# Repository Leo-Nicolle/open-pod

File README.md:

# opentone

Work in progress.

This is a mp3 player in the style of an ipod classic. 

### Hardware
 - MCU: ESP32
 - Display: 2.2" LCD
 - SD Card: MicroSD
 - Audio: VS1063
 - Click wheel: MPR121

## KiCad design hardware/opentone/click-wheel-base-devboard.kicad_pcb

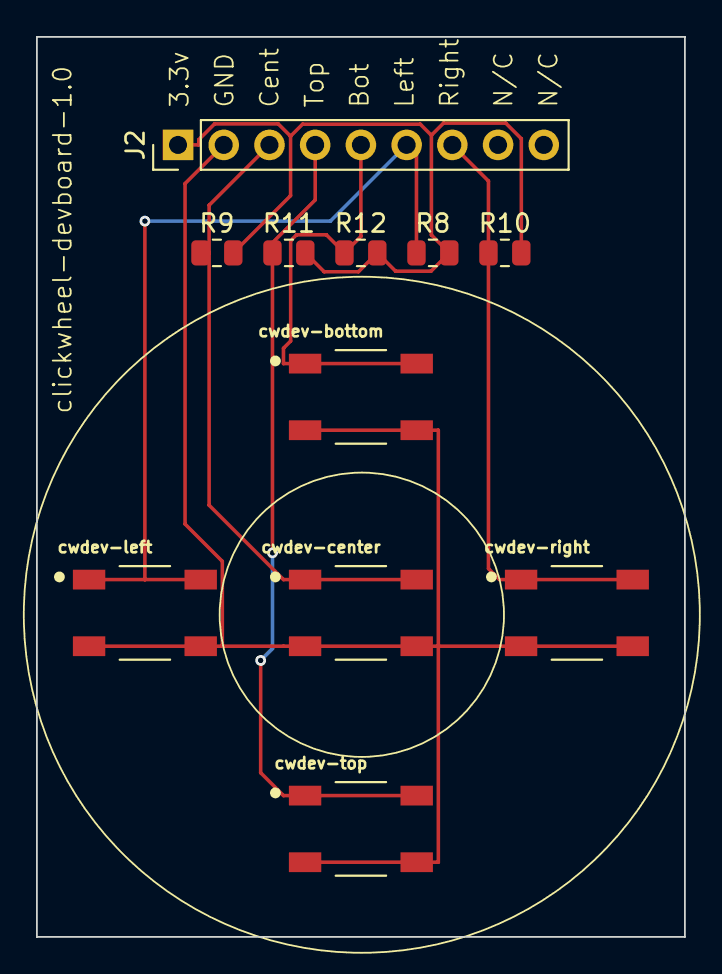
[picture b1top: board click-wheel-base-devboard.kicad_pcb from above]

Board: 2 copper layers, 36.0 x 50.0 mm, 11 parts (0 on the bottom side), 7 nets.

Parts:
J2: Conn_01x09; PinHeader_1x09_P2.54mm_Vertical
R8, R9, R10, R11, R12: 10k; R_0805_2012Metric
cwdev-bottom: SKQGAFE010; SW_SKQGAFE010
cwdev-center: SKQGAFE010; SW_SKQGAFE010
cwdev-left: SKQGAFE010; SW_SKQGAFE010
cwdev-right: SKQGAFE010; SW_SKQGAFE010
cwdev-top: SKQGAFE010; SW_SKQGAFE010

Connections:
+3.3V: J2.1, R8.2, R9.2, R10.2, R11.2, R12.2
GND: J2.2, cwdev-bottom.3, cwdev-bottom.4, cwdev-center.3, cwdev-center.4, cwdev-left.3, cwdev-left.4, cwdev-right.3, cwdev-right.4, cwdev-top.3, cwdev-top.4
SW_BOTTOM: J2.5, R12.1, cwdev-bottom.1, cwdev-bottom.2
SW_CENTER: J2.3, R9.1, cwdev-center.1, cwdev-center.2
SW_LEFT: J2.6, R8.1, cwdev-left.1, cwdev-left.2
SW_RIGHT: J2.7, R10.1, cwdev-right.1, cwdev-right.2
SW_TOP: J2.4, R11.1, cwdev-top.1, cwdev-top.2

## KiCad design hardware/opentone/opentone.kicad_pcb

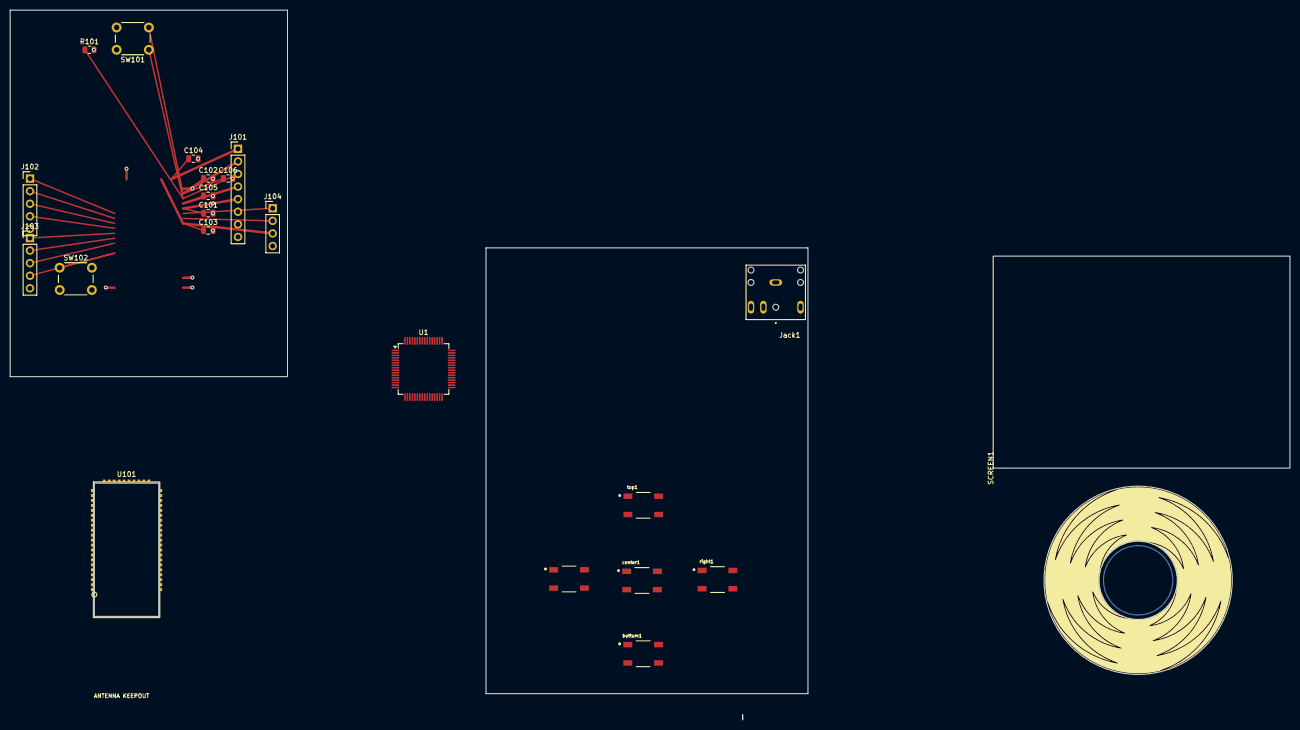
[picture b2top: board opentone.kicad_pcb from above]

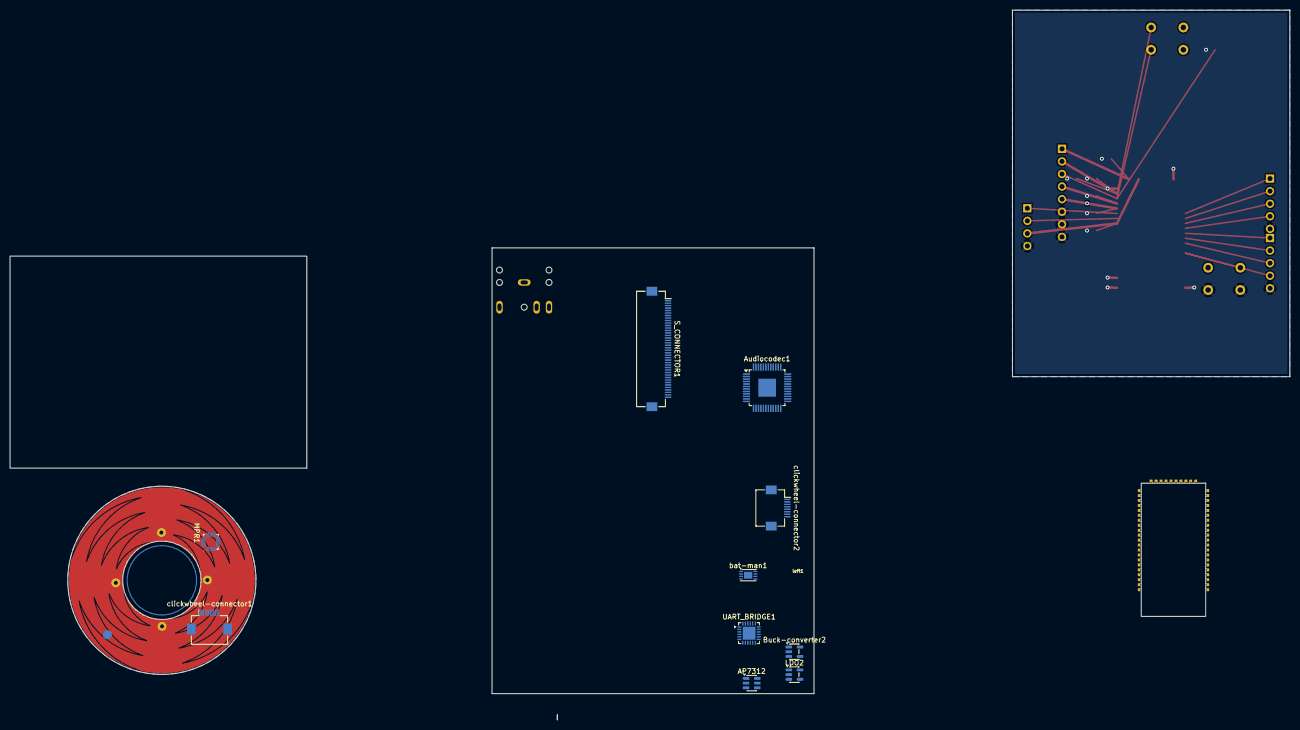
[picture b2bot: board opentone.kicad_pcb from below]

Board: 2 copper layers, 258.4 x 143.3 mm, 33 parts (10 on the bottom side), 42 nets.

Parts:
AP7312: SOT-23-6
Audiocodec1: VS1063; LQFP-48-1EP_7x7mm_P0.5mm_EP3.6x3.6mm
Buck-converter2: LM3671; TSOT-23-5
C101, C102, C103, C104, C105: 100n; C_0805_2012Metric
C106: 10u; C_0805_2012Metric
Clickwheel1: clickwheel_1
J101: POWER; PinHeader_1x08_P2.54mm_Vertical
J102: UART; PinHeader_1x05_P2.54mm_Vertical
J103: DEBUG; PinHeader_1x05_P2.54mm_Vertical
J104: USB; PinHeader_1x04_P2.54mm_Vertical
Jack1: SJ1-3524NG; CUI_SJ1-3524NG
LDO2: MIC5504-3.3YM5; SOT-23-5
MPR1: MPR121QR2; mpr121qr2
R101: 100k; R_0805_2012Metric
SCREEN1: nhd-2.4-240320cf-ctxif
SW101: PWR; SW_PUSH_6mm_H4.3mm
SW102: RST; SW_PUSH_6mm_H4.3mm
S_CONNECTOR1: Hirose_FH12-40S-0.5SH_1x40-1MP_P0.50mm_Horizontal
U1: STM32F446RCTx; LQFP-64_10x10mm_P0.5mm
U101: FSC-BT1035; fsc-bt1035
UART_BRIDGE1: CP2102N-Axx-xQFN24; QFN-24-1EP_4x4mm_P0.5mm_EP2.6x2.6mm
bat-man1: MCP73831-2-MC; DFN-8-1EP_3x2mm_P0.5mm_EP1.7x1.4mm
bottom1: SKQGAFE010; SW_SKQGAFE010
center1: SKQGAFE010; SW_SKQGAFE010
clickwheel-connector1, clickwheel-connector2: Hirose_FH12-8S-0.5SH_1x08-1MP_P0.50mm_Horizontal
left1: SKQGAFE010; SW_SKQGAFE010
right1: SKQGAFE010; SW_SKQGAFE010
top1: SKQGAFE010; SW_SKQGAFE010

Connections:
3.3-audio: AP7312.1 (OUT2), LDO2.5 (VOUT)
3.3V: LDO2.1 (VIN), LDO2.3 (EN)
+3.3V: AP7312.3 (EN2), AP7312.4 (EN1), AP7312.5 (IN)
AVDD: Audiocodec1.38 (AVDD0), Audiocodec1.43 (AVDD1), Audiocodec1.45 (AVDD2)
BT_1V8: C105.1, J101.4, U101.35
BT_3V3: C104.1, J101.1, U101.31
BT_CTS: J102.2, U101.15
BT_GND: C101.2, C102.2, C103.2, C104.2, C105.2, C106.2, J101.6, J101.7, J101.8, J102.5, J103.5, J104.4, R101.2, SW102.2, U101.1, U101.22, U101.32, U101.50, U101.52
BT_PIO6: J103.3, U101.10
BT_PIO7: J103.2, U101.11
BT_PIO8: J103.1, U101.12
BT_RESET: J103.4, SW102.1, U101.8
BT_RTS: J102.1, U101.16
BT_RX: J102.3, U101.14
BT_SYS_CTRL: J101.3, R101.1, SW101.1, U101.34
BT_TX: J102.4, U101.13
BT_USB_DN: J104.2, U101.38
BT_USB_DP: J104.1, U101.37
BT_VBAT: C102.1, C106.1, J101.2, SW101.2, U101.33
BT_VCHG: C103.1, J104.3, U101.29, U101.39
BT_VDD_IO: C101.1, J101.5, U101.36
CVDD: Audiocodec1.5 (CVDD0), Audiocodec1.7 (CVDD1), Audiocodec1.24 (CVDD2), Audiocodec1.31 (CVDD3)
GND: AP7312.2 (GND), Audiocodec1.4 (DGND0), Audiocodec1.16 (DGND1), Audiocodec1.20 (DGND2), Audiocodec1.21 (DGND3), Audiocodec1.22 (DGND4), Audiocodec1.35 (GND), Audiocodec1.37 (AGND0), Audiocodec1.40 (AGND1), Audiocodec1.41 (AGND2), Audiocodec1.47 (AGND3), Buck-converter2.2 (GND), Clickwheel1.5 (GND), LDO2.2 (GND), UART_BRIDGE1.2 (GND), UART_BRIDGE1.25 (GND), bat-man1.6 (V_{SS})
GPIO_PULL: Audiocodec1.9 (GPIO2/DCLK), Audiocodec1.10 (GPIO3/SDATA), Audiocodec1.11 (GPIO6/I2S_SCLK), Audiocodec1.12 (GPIO7/I2S_SDATA), Audiocodec1.25 (GPIO5/I2S_MCLK), Audiocodec1.33 (GPIO0), Audiocodec1.34 (GPIO1), Audiocodec1.36 (GPIO4/I2S_LROUT)
IOVDD: Audiocodec1.6 (IOVDD0), Audiocodec1.14 (IOVDD1), Audiocodec1.19 (IOVDD2), Audiocodec1.32 (XTEST)
unnamed: Buck-converter2.3 (EN), Buck-converter2.4 (FB)
unnamed: UART_BRIDGE1.5 (VIO), UART_BRIDGE1.6 (VDD)
unnamed: bat-man1.1 (V_{DD}), bat-man1.2 (V_{DD})
unnamed: Clickwheel1.1 (top), MPR1.16 (ELEC8)
unnamed: Clickwheel1.2 (right), MPR1.15 (ELEC7)
unnamed: Clickwheel1.3 (bottom), MPR1.19 (ELEC11)
unnamed: Clickwheel1.4 (left), MPR1.9 (ELEC1)
unnamed: MPR1.1 (~IRQ), clickwheel-connector1.2 (IRQ)
unnamed: MPR1.2 (SCL), clickwheel-connector1.3 (SCL)
unnamed: MPR1.3 (SDA), clickwheel-connector1.4 (SDA)
unnamed: MPR1.4 (ADDR), clickwheel-connector1.5 (ADDR)
unnamed: MPR1.5 (VREG), clickwheel-connector1.6 (VREG)
unnamed: MPR1.6 (VSS), clickwheel-connector1.7 (VSS)
unnamed: MPR1.7 (REXT), clickwheel-connector1.8 (REXT)
unnamed: MPR1.20 (VDD), clickwheel-connector1.1 (VDD)
unnamed: U1.18 (VSS), U1.31 (VSS), U1.47 (VSS), U1.63 (VSS)
VBAT: bat-man1.3 (V_{BAT}), bat-man1.4 (V_{BAT})

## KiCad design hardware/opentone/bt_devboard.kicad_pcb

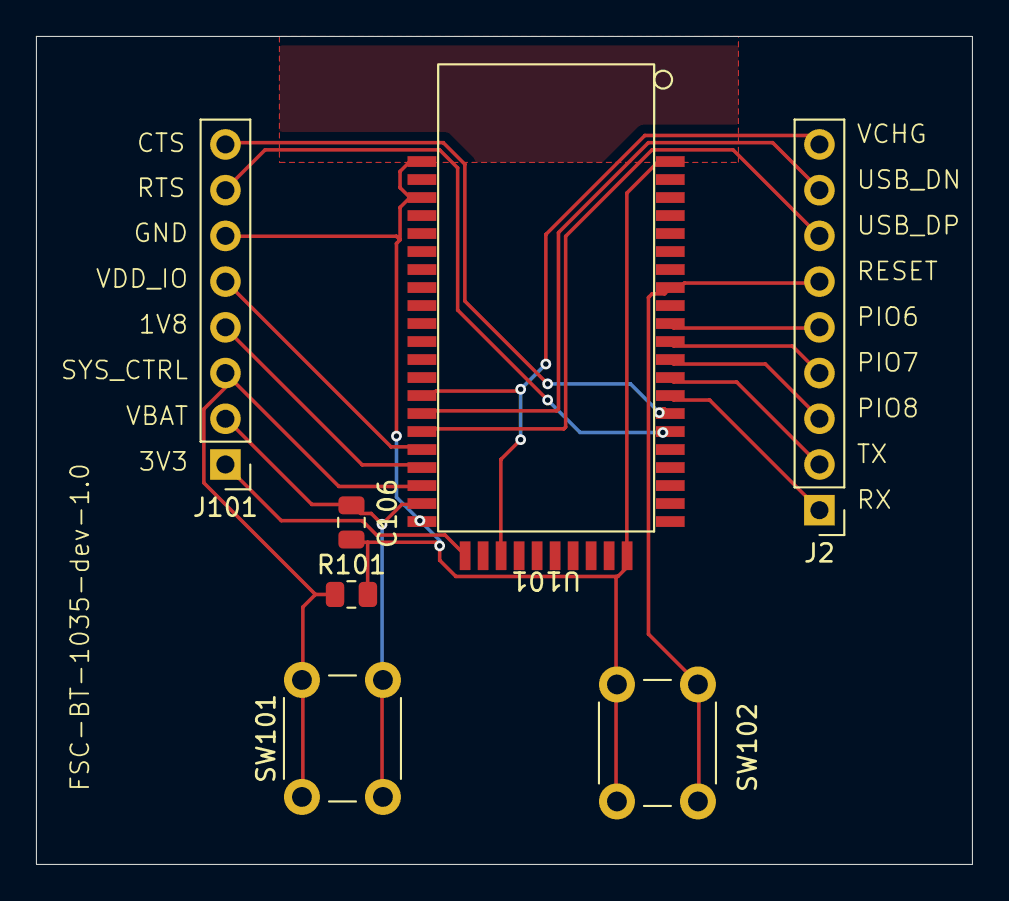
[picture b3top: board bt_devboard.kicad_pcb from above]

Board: 2 copper layers, 52.0 x 46.0 mm, 7 parts (0 on the bottom side), 17 nets.

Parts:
C106: 10u; C_0805_2012Metric
J2: Conn_01x09; PinHeader_1x09_P2.54mm_Vertical
J101: POWER; PinHeader_1x08_P2.54mm_Vertical
R101: 100k; R_0805_2012Metric
SW101: PWR; SW_PUSH_6mm_H4.3mm
SW102: RST; SW_PUSH_6mm_H4.3mm
U101: FSC-BT1035; fsc-bt1035

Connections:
/BT_1V8: J101.4, U101.35 (1.8V_OUT)
/BT_3V3: J101.1, U101.31 (VDD_USB/3.3V_OUT)
/BT_CTS: J101.8, U101.15 (BT_CTS/PIO3)
/BT_GND: C106.2, J101.6, R101.2, SW102.2, U101.1 (GND), U101.22 (GND), U101.32 (GND), U101.50 (GND), U101.52 (GND)
/BT_PIO6: J2.5, U101.10 (PIO6)
/BT_PIO7: J2.4, U101.11 (PIO7)
/BT_PIO8: J2.3, U101.12 (PIO8)
/BT_RESET: J2.6, SW102.1, U101.8 (RESET)
/BT_RTS: J101.7, U101.16 (BT_RTS/PIO2)
/BT_RX: J2.1, U101.14 (BT_RX/PIO4)
/BT_SYS_CTRL: J101.3, R101.1, SW101.1, U101.34 (SYS_CTRL)
/BT_TX: J2.2, U101.13 (BT_TX/PIO5)
/BT_USB_DN: J2.8, U101.38 (USB_D-)
/BT_USB_DP: J2.7, U101.37 (USB_D+)
/BT_VBAT: C106.1, J101.2, SW101.2, U101.33 (VBAT_IN)
/BT_VCHG: J2.9, U101.29 (VCHG_SENSE), U101.39 (VCHG)
/BT_VDD_IO: J101.5, U101.36 (VDD_IO)

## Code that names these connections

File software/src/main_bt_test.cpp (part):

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//   !hex           toggle the hex dump of what the module sends
//   !pin           read the levels of the BT pins
//
// Audio over I2S (VS1053 GPIO4/6/7 -> module PCM_SYNC/CLK/IN):
//   !i2s           module input = I2S slave 48 kHz 16 bit, VS1053 I2S on
//   !tone          VS1053 sine test on/off
//   !play          loop the startup sound (MP3 from flash), !stop to stop
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static void printPins()
{
  // BT_TX idles high once the module runs its UART; low or floating while off.
  Serial.printf("SYS_CTRL (PA15) out=%d | BT_TX -> PB7 reads %d\n",
                digitalRead(BT_SYS_CTRL), digitalRead(BT_UART_RX));
}

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  Serial.printf("VS1053 volume %u\n", v);
}

// VS1053 datasheet 11.14: GPIO4-7 as outputs, then I2S_CONFIG = enable at
// 48 kHz. As I2S master at 48 kHz, SCLK = 12.288 MHz / 8 = 1.536 MHz, i.e.
// 16-bit words: that's the module's AT+I2SCFG=3 (slave, 48 kHz, 16 bit, I2S).
// MCLK stays off: the module doesn't need it.
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}

// Reads the VS1053's own pin levels (GPIO_IDATA, 0xC018) many times over SCI.
// With I2S running, LROUT (GPIO4) and SCLK (GPIO6) must be seen both high and
// low, and SDATA (GPIO7) too while sound plays. A pin stuck at one level is
// either not driven or shorted/loaded by the wiring.
static void checkI2S()
{
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  {
    uint8_t bit;
    const char *name;
  } pins[] = {{4, "GPIO4 LROUT -> PCM_SYNC (7)"},
              {6, "GPIO6 SCLK  -> PCM_CLK  (4)"},
              {7, "GPIO7 SDATA -> PCM_IN   (5)"}};
  for (auto &pin : pins)
  {
    bool h = seenHigh & (1 << pin.bit), l = seenLow & (1 << pin.bit);
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
  // SYS_CTRL has no internal pull: drive it low right away (module off).
  digitalWrite(BT_SYS_CTRL, LOW);
  pinMode(BT_SYS_CTRL, OUTPUT);
  pinMode(BT_UART_RX, INPUT); // read the module's TX level before the UART

  Serial.begin(115200);
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
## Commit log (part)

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2019-07-28 rename player to state
2019-07-29 play mp3 file
2019-07-30 put sd screen and player togethter
2019-07-30 read data files and display them
2019-07-30 better read files: compute max lines and use 128 length lines
2019-07-30 added menus and navigate into them
2019-07-30 added backward function
2020-01-03 rewiring
2020-01-03 fix problems rewiring
2020-03-29 new screen
2020-04-02 add touch + update code for new display
2020-04-10 new display start refacto
2020-04-10 fix printing menus on screen
2020-04-10 draw a battery
2020-04-11 better state: store line into menuState
2020-04-11 clean screen on file change
2020-04-17 first version of sensing wheel for scrolling
2020-04-17 magic hat: fix display problem ... weird
2020-12-26 WIP switch to esp32
2022-10-18 removed display
2022-10-21 added OTA
2022-10-21 added clickwheel and debug
2022-10-22 use constants for urls and passwrods
2022-10-23 better scroll
2024-07-08 click wheel pinout
2025-05-08 rebirth
2025-05-09 restart
2025-05-09 added docs
2025-05-10 try to make it svg2mod compatible
2025-05-11 split in components
2025-05-11 update clickwheel component
2025-05-11 fixed reactivity + deploy scripts
2025-05-11 favicon
2025-05-11 cleanup
2025-05-11 readme
2025-05-12 designed clickwheel and see if mpr121 can fit on it
2025-05-15 update power and audio
2025-05-15 added UART converter
2025-05-18 added bluetooth
2025-05-23 try up with vs1053 feather
2025-05-23 setupt the player file
2025-05-31 fill screen with different colors
2025-05-31 almost works with GFX, just wrong coordinates
2025-05-31 test MADCTL 1
2025-05-31 wrong, screen is all white
2025-05-31 screen pins before remap
2025-05-31 new pinout with consecutive 16bits on the PCs pins
2025-05-31 screen works
2025-05-31 added demo
2025-05-31 updated platformio.ini
2025-05-31 added blog
2025-06-01 first menu
2025-06-01 Fast (ugly) menu renderer
2025-06-01 ugly theme + blog post
2025-06-02 transition using HW scrolling
2025-06-03 breakdown ui
2025-06-03 30 rows buffer
2025-06-03 remove row/col shit
2025-06-03 added content for the blog
2025-06-03 start restoring render of the now playing
2025-06-07 scroll to nowplaying
2025-06-07 working transitiontotracklist (but slight prolbem with last line)
2025-06-07 fixed the wrapping issue at the bottom
2025-06-07 update theme
2025-06-08 rewired vs1053
2025-06-08 screen and mp3 working
2025-06-08 pins
2025-06-08 updated mp3 pinout to have i2c available
2025-06-08 testing the clickwheel with teleplot: looking good !
2025-06-09 Debugging the wheel: it follows my finger on the screen
2025-06-09 first scrolling the tracks with the wheel !
2025-06-10 use an app state and allow to use more bits per pixel
2025-06-10 setup unit tests
2025-06-10 remove select track
2025-06-13 use doctest and reporter
2025-06-13 make tests pass
2025-06-13 fixed scripts
2025-06-13 faster render fonts
2025-06-13 dark background
2025-06-14 better state + events handler system
2025-06-15 faster renderer of tracklist + animations + better split between concerns
2025-06-15 2 bits per pixel
2025-06-16 docs
2025-06-16 remove unit tests
2025-06-16 simplify ui list
2025-06-16 rename track to element
2025-06-16 psram controller
2025-06-16 psram works on SPI1
2025-06-16 psram controller works
2025-06-17 indexer
2025-06-17 crawler
2025-06-17 radix tree?
2025-06-17 update trie generator
2025-06-17 started implementing storage
2025-06-17 trie index
2025-06-22 search works on the stm32
2025-06-22 can retrieve now paths
2025-06-23 sound player on the way
2025-06-23 enhanced mp3 working, but not flac
2025-06-23 flac plugin
2025-06-23 config files
2025-06-23 load flac plugin correctly: saccaded sound
2025-06-23 cleaning up
2025-06-23 FLAC plays (faster PRSRAM)
2025-06-23 wip: DMA
2025-06-23 DMA works
2025-06-23 larger buffer, better speed cause less overhead
2025-06-26 DMA controller
2025-06-26 removed DMA, was not working properlly, came back to SPI (0.73MB/s)
2025-06-26 reorganize
2025-06-26 updated index: generate all the hashmaps
2025-06-26 added more indexes
2025-06-26 almost have a working lookup, only addressing/serializing/unserializin error away
2025-06-27 indexer and lookup works
2025-06-30 added router
2025-07-01 load state and route
2025-07-01 wip improved navigation
2025-07-01 proper back and forth transitions
2025-07-01 complete navigation
2025-07-06 Rebirth (#2)
    * designed clickwheel and see if mpr121 can fit on it
    * update power and audio
    * added UART converter
    * added bluetooth
    * try up with vs1053 feather
    * setupt the player file
